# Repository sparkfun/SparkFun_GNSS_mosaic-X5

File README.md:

SparkFun Tri-band GNSS RTK Breakout - mosaic-X5
========================================

[*SparkFun Tri-band GNSS RTK Breakout - mosaic-X5 (GPS-23088)*](https://www.sparkfun.com/sparkfun-triband-gnss-rtk-breakout-mosaic-x5.html)

At the heart of the Triband GNSS RTK Breakout is [Septentrio](https://www.septentrio.com/en)'s mosaic-X5, a compact, low power, multi-band, multi-constellation, high-precision GNSS receiver. The receiver supports the GPS (USA), GLONASS (Russia), Beidou (China), Galileo (Europe), and NavIC (India) constellations, including regional systems *(i.e. SBAS and QZSS)*. With its [**Real Time Kinematics**](https://learn.sparkfun.com/tutorials/813) (RTK) capabilities, the module can achieve a horizontal accuracy of 6mm (~0.25in), vertical accuracy of 1cm (~0.4in) using RTK, and timing precision of 5ns (5 billionths of a second). It also features Septentrio's unique [AIM+ technology](https://www.septentrio.com/en/learn-more/advanced-positioning-technology/aim-jamming-protection) for interference mitigation and anti-spoofing, ensuring best-in-class reliability and scalable position accuracy.

The mosaic-X5 is a sophisticated chip running an internal web server that can be accessed through the USB interface with a standard browser using a Linux/Windows computer. Septentrio also provides dozens of [video tutorials](https://www.youtube.com/@SeptentrioGNSS/videos) to guide users through the configuration settings of their GNSS receivers utilizing the web interface.

Beyond the capabilities of the mosaic-X5 module, this board is seamless to operate with no programming skills required. Gone are the times when a microcontroller was required to interface with the GNSS receiver and log data to an SD card and when users had to carry around an SD card reader to extract the data from the SD card. The mosaic-X5 Triband GNSS RTK Breakout can start/stop logging data or mount/unmount the SD card, without a single line of code, just utilizing a simple button. For the users who prefer a command-line interface, Septentrio has you covered. Users can still control and configure the mosaic-X5 module through a CLI, which is useful for scenarios such as production line testing *(in fact, that is how we tested this board)*.

This breakout board is a perfect middle ground for users who would like to integrate the mosaic-X5 module into a project/enclosure with access to a majority of the module's available pins, similar to Septentrio's developer kit, but in the smaller form factor of their evaluation kit. Or maybe... you just needed a PPS output at a 3.3V logic level. *Please, check out our [hookup guide](https://docs.sparkfun.com/SparkFun_GNSS_mosaic-X5) for more details on the capabilities of this board (that we couldn't fit in this product description).*

Documentation
--------------

- **[Hookup Guide (mkdocs)](http://docs.sparkfun.com/SparkFun_GNSS_mosaic-X5/)** - Hookup guide for the mosaic-X5 GNSS Breakout hosted by GitHub pages.<br>

Repository Contents
-------------------

- **[/docs](/docs/)** - Online documentation files
  - [assets](/docs/assets/) - Assets files
    - [board_files](/docs/assets/board_files/) - Files for the product design
      - [Eagle design files](/docs/assets/board_files/eagle_files.zip) (.zip)
      - [Schematic](/docs/assets/board_files/schematic.pdf) (.pdf)
      - [Dimensions](/docs/assets/board_files/dimensions.pdf) (.pdf)
    - [component_documentation](/docs/assets/component_documentation/) - Datasheets for hardware components
    - [img/hookup_guide/](/docs/assets/img/hookup_guide/) - Images for hookup guide documentation
- **[/Hardware](/Hardware/)** - Eagle design files (.brd, .sch)
  - **[/Production](/Production/)** - Production files

Product Variants
----------------

- mosaic-X5:
  - [GPS-23088](https://www.sparkfun.com/sparkfun-triband-gnss-rtk-breakout-mosaic-x5.html) - Triband GNSS RTK Breakout - mosaic-X5
  - [SXM-E](https://www.sparkpnt.com/products/sparkpnt-sxm-e-cors) - RTK mosaic-X5
  - [GPS-24903](https://www.sparkfun.com/sparkpnt-rtk-facet-mosaic-l-band.html) - SparkPNT RTK Facet mosaic L-Band
  - Flex Modules:
    - [GPS-28138](https://www.sparkfun.com/sparkpnt-gnss-flex-module-mosaic-x5.html) - GNSS Flex module - mosaic-X5
    - [GPS-29457](https://www.sparkfun.com/sparkpnt-gnss-flex-module-mosaic-x5-im19-imu.html) - GNSS Flex module - mosaic-X5 & IM19
    - [GPS-28766](https://www.sparkfun.com/sparkfun-gnss-flex-phat-mosaic-x5.html) - GNSS Flex pHAT w/ the mosaic-X5 GNSS Flex module
    - [GPS-29889](https://www.sparkfun.com/sparkfun-gnss-flex-phat-mosaic-x5-im19-imu.html) - GNSS Flex pHAT w/ the mosaic-X5 & IM19 GNSS Flex module
- mosaic-G5 P3:
  - [GPS-29208]( - GNSS RTK Breakout - mosaic-G5 P3
  - Flex Modules:
    - [GPS-29209](https://www.sparkfun.com/sparkpnt-gnss-flex-module-mosaic-g5-p3.html) - GNSS Flex module - mosaic-G5 P3
    - [GPS-29363](https://www.sparkfun.com/sparkpnt-gnss-flex-module-mosaic-g5-p3-im19-imu.html) - GNSS Flex module - mosaic-G5 P3 & IM19
    - [GPS-](https://www.sparkfun.com/sparkfun-gnss-flex-phat-mosaic-g5-p3.html) - GNSS Flex pHAT w/ the mosaic-G5 P3 GNSS Flex module
    - [GPS-](https://www.sparkfun.com/sparkfun-gnss-flex-phat-mosaic-g5-p3-im19-imu.html) - GNSS Flex pHAT w/ the mosaic-G5 P3 & IM19 GNSS Flex module
- mosaic-T:
  - [GPS-28731](https://www.sparkfun.com/sparkfun-timing-gnss-breakout-mosaic-t.html) - mosaic-T Timing GNSS Breakout
  - [SXT](https://www.sparkpnt.com/products/sxt-gnssdo) - GNSS Disciplined Oscillator

Version History
---------------

- [v10](https://github.com/sparkfun/SparkFun_GNSS_mosaic-X5/releases/tag/v10) - Initial Release

License Information
-------------------

This product is ***open source***!

Please review the [`LICENSE.md`](./LICENSE.md) file for license information.

If you have any questions or concerns about licensing, please contact technical support on our [SparkFun forums](https://community.sparkfun.com/).

Distributed as-is; no warranty is given.

- Your friends at SparkFun.

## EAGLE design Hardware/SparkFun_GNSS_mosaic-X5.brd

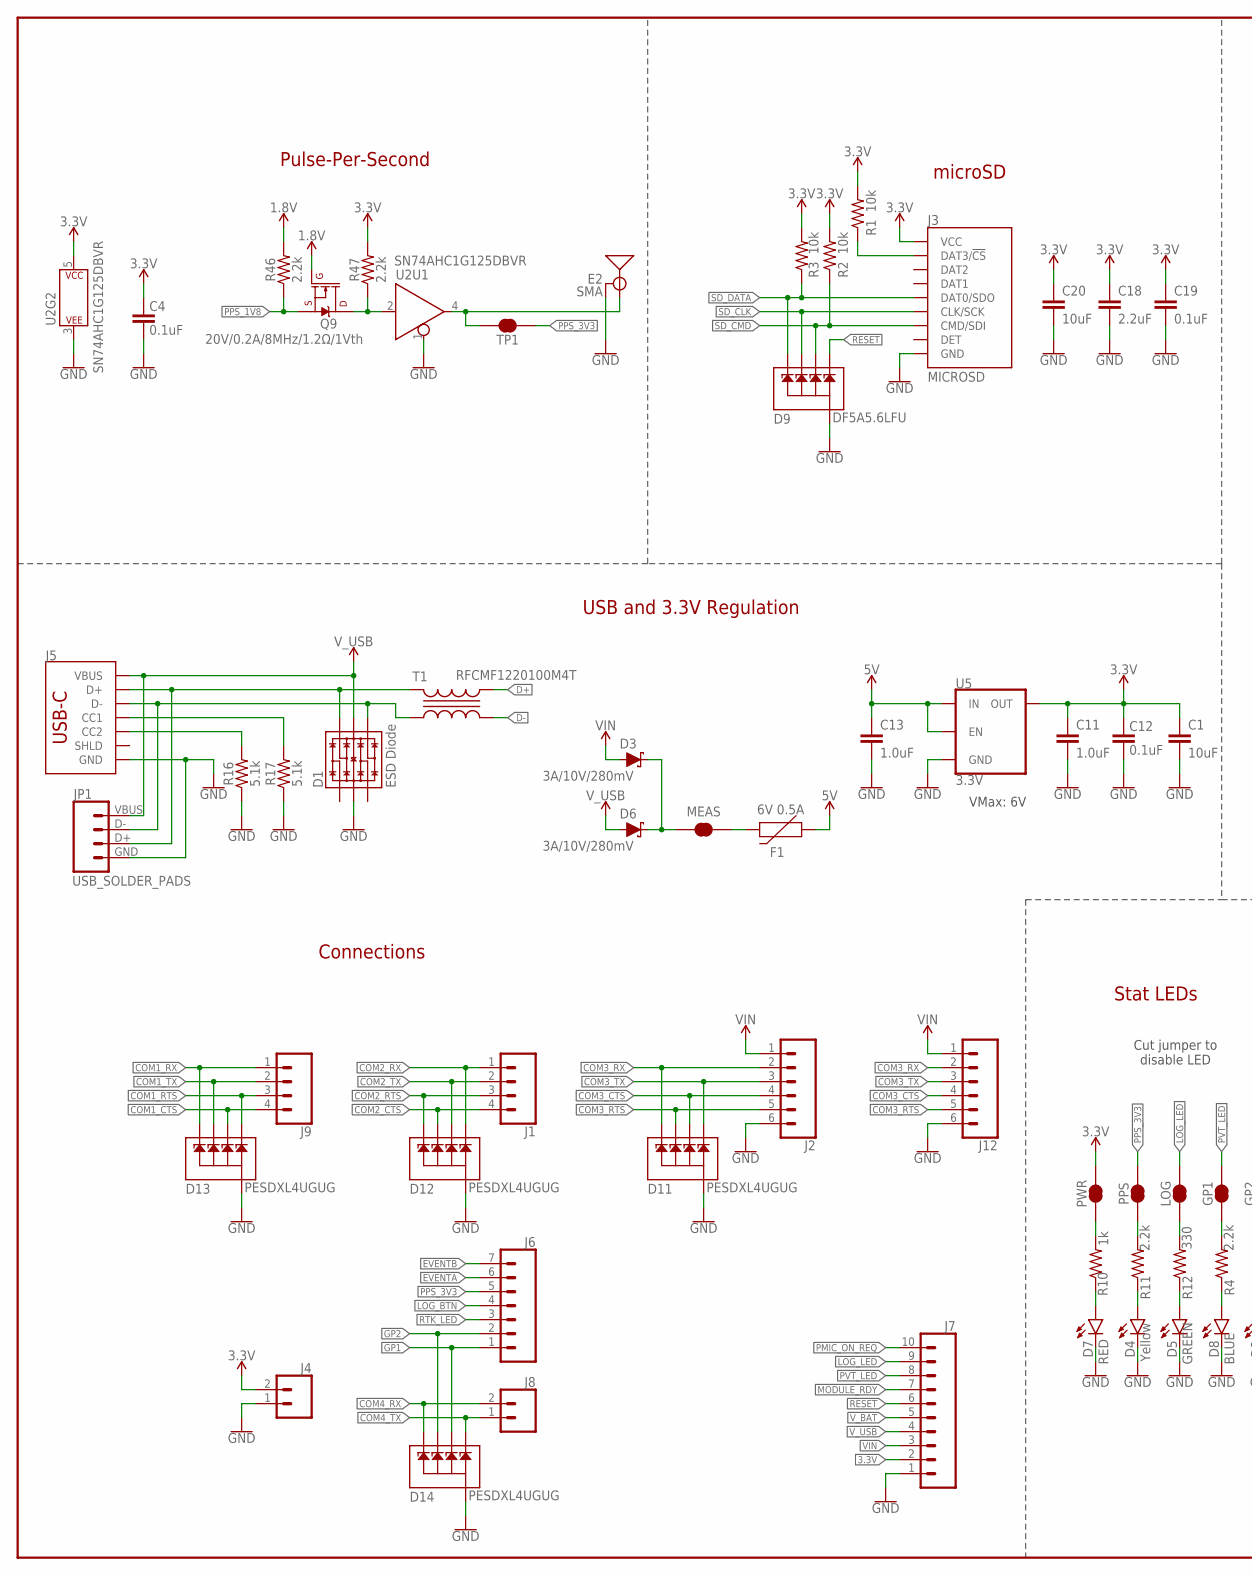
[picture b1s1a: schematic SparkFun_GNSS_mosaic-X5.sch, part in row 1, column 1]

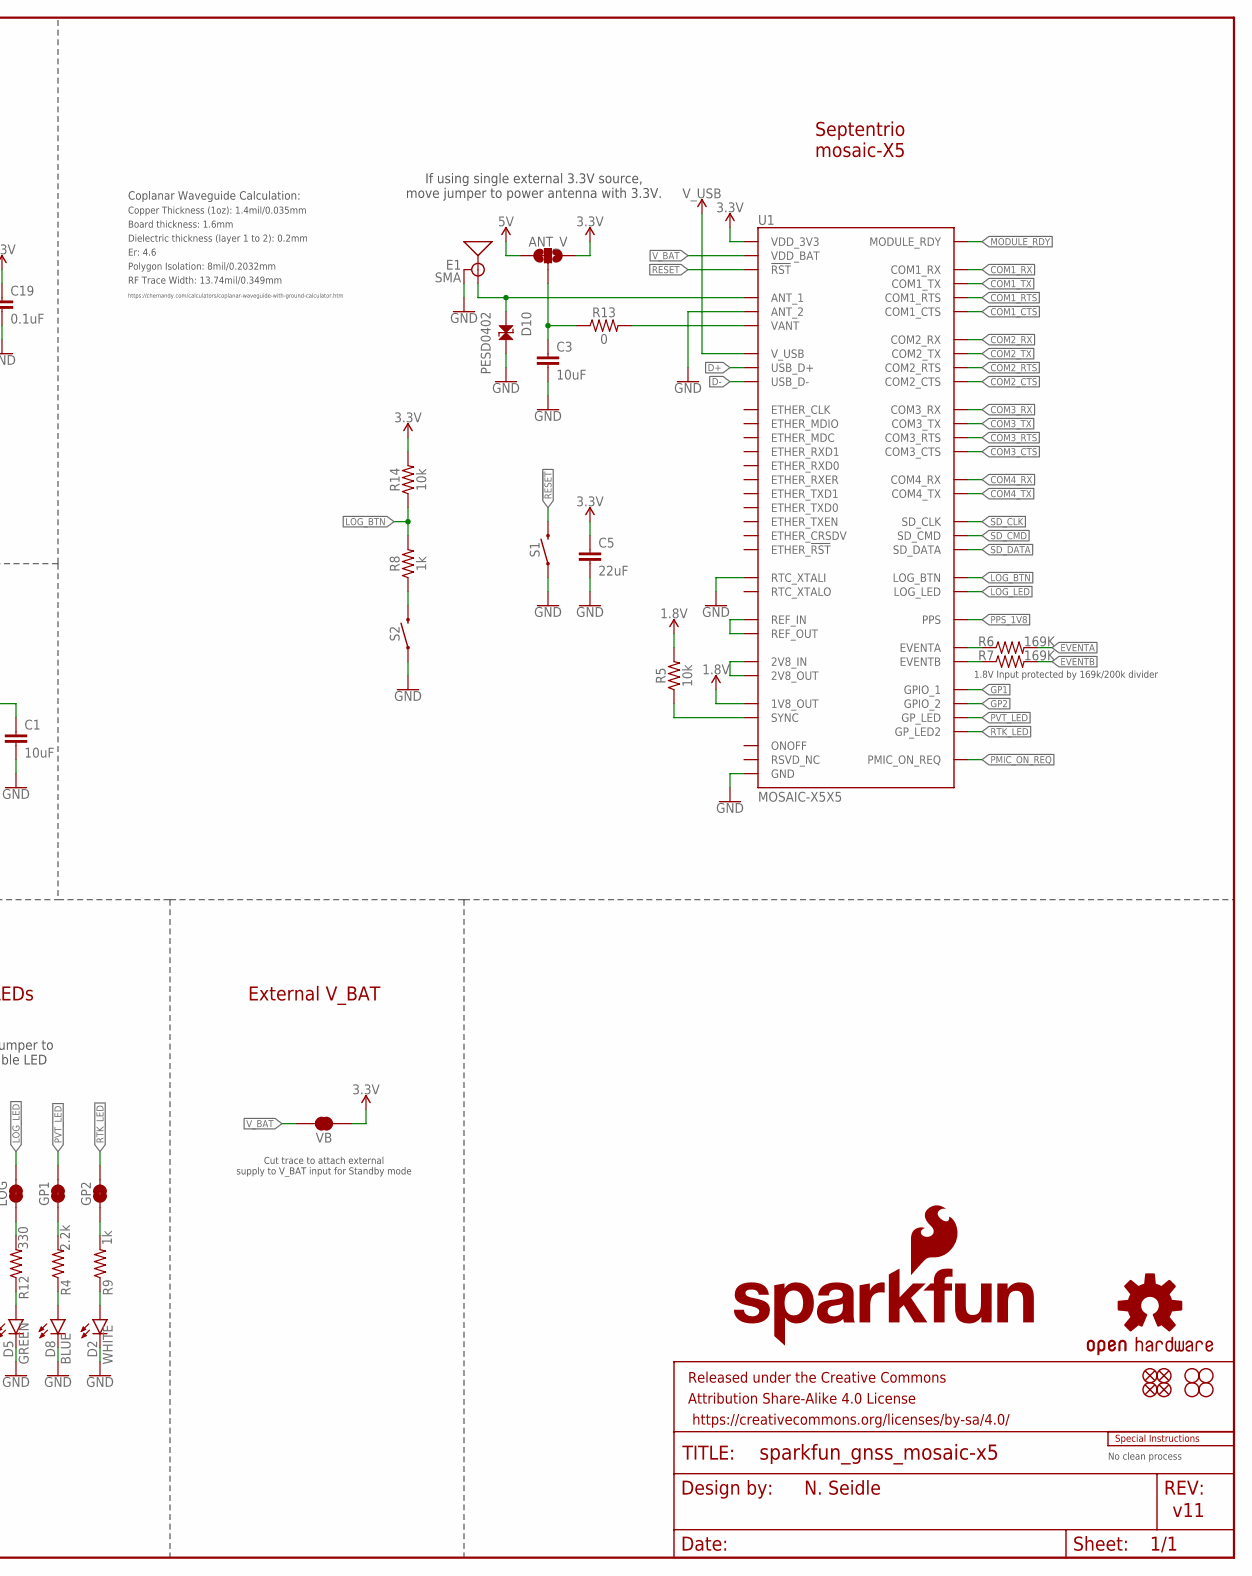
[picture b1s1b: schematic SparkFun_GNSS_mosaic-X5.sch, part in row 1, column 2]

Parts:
ANT_V: JUMPER-SMT_3_1-NC_TRACE_SILK; SMT-JUMPER_3_1-NC_TRACE_SILK
C1, C3, C20: 10uF; 0603
C4, C12, C19: 0.1uF; 0603
C5: 22uF; 0603
C11, C13: 1.0uF; 0603
C18: 2.2uF; 0603
D1: ESD Diode; SOT-23-6
D2: WHITE; LED-0603
D3, D6: 3A/10V/280mV; SOD-323
D4: Yellow; LED-0603
D5: GREEN; LED-0603
D7: RED; LED-0603
D8: BLUE; LED-0603
D9: DF5A5.6LFU; SOT353
D10: PESD0402; 0402-TIGHT
D11, D12, D13, D14: PESDXL4UGUG; SOT353
E1, E2: SMA; SMA-EDGE
F1: 6V 0.5A; 0805
FRAME2: FRAME-LEDGER; CREATIVE_COMMONS
GP1, GP2: JUMPER-SMT_2_NC_TRACE_SILK; SMT-JUMPER_2_NC_TRACE_SILK
H1, H2, H3, H4: STAND-OFF
J1, J9: CONN_041X04_NO_SILK_NO_POP; 1X04_NO_SILK
J2: CONN_06JST-SMD-LOCKING; JST-6-SMD-1.25MM-LOCKING
J3: MICROSD; MICROSD-EXTERNALPIN
J4, J8: CONN_021X02_NO_SILK; 1X02_NO_SILK
J5: USB Female Type C Connector; USB-C-16P_4LAYER-PADS
J6: CONN_07NO_SILK; 1X07_NO_SILK
J7: CONN_10NO_SILK_PTH_FEMALE; 1X10_NO_SILK
J12: CONN_06PAD; 1X06_SOLDER_PADS
JP1: USB_SOLDER_PADS; USB-SOLDER-PADS
JP21, JP61, JP71, JP81: FIDUCIALUFIDUCIAL; FIDUCIAL-MICRO
LOG: JUMPER-SMT_2_NC_TRACE_SILK; SMT-JUMPER_2_NC_TRACE_SILK
LOGO2: OSHW-LOGOMINI; OSHW-LOGO-MINI
LOGO4: SFE_LOGO_NAME_FLAME10_MM; SFE_LOGO_NAME_FLAME_10MM
MEAS: JUMPER-COMBO_2_NC_TRACE; COMBO-JUMPER_2_NC_TRACE
PPS: JUMPER-SMT_2_NC_TRACE_SILK; SMT-JUMPER_2_NC_TRACE_SILK
PWR: JUMPER-SMT_2_NC_TRACE_SILK; SMT-JUMPER_2_NC_TRACE_SILK
Q9: 20V/0.2A/8MHz/1.2Ω/1Vth; SOT-416FL
R1, R2, R3, R5, R14: 10k; 0603
R4, R11, R46, R47: 2.2k; 0603
R6, R7: 169K; 0603
R8, R9, R10: 1k; 0603
R12: 330; 0603
R13: 0; 0603
R16, R17: 5.1k; 0603
S1: MOMENTARY-SWITCH-SPST-SMD-4.6X2.8MM; TACTILE_SWITCH_SMD_4.6X2.8MM
S2: MOMENTARY-SWITCH-SPST-SMD-5.2-TALL-REDUNDANT; TACTILE_SWITCH_SMD_5.2MM
T1: RFCMF1220100M4T
TP1: JUMPER-SMT_2_NC_TRACE_SILK; SMT-JUMPER_2_NC_TRACE_SILK
U1: MOSAIC-X5X5; MOSAIC_LGA
U2: SN74AHC1G125DBVR; SOT23-5
U5: 3.3V; SOT23-5
U$2: SPECIAL_INSTRUCTIONS-ORDERING; ORDERING_INSTRUCTIONS
VB: JUMPER-SMT_2_NC_TRACE_SILK; SMT-JUMPER_2_NC_TRACE_SILK

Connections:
1.8V: Q9.1 (G), R5.2, R46.2, U1.AC4 (1V8_OUT)
3.3V: ANT_V.1, C1.1, C4.2, C5.1, C11.1, C12.2, C18.1, C19.1, C20.1, J3.4 (VCC), J4.2, J7.2, PWR.2, R1.2, R2.2, R3.2, R14.2, R47.2, U1.A18 (VDD_3V3), U1.A19 (VDD_3V3), U1.A20 (VDD_3V3), U1.B18 (VDD_3V3), U1.B19 (VDD_3V3), U1.B20 (VDD_3V3), U1.C18 (VDD_3V3), U1.C19 (VDD_3V3), U1.C20 (VDD_3V3), U2.5 (P$V+), U5.5 (OUT), VB.1
5V: ANT_V.3, C13.1, F1.1, U5.1 (IN), U5.3 (EN)
!RESET!: D9.3, J7.6, S1.3 (2), S1.4 (2), U1.A11 (!RST!)
ANT_V: ANT_V.2, C3.1, R13.1
CC1: J5.A5 (CC1), R17.2
CC2: J5.B5 (CC2), R16.2
COM1_CTS: D13.4, J9.4, U1.E1 (COM1_CTS)
COM1_RTS: D13.3, J9.3, U1.C1 (COM1_RTS)
COM1_RX: D13.1, J9.1, U1.B1 (COM1_RX)
COM1_TX: D13.5, J9.2, U1.D1 (COM1_TX)
COM2_CTS: D12.5, J1.4, U1.J1 (COM2_CTS)
COM2_RTS: D12.1, J1.3, U1.G1 (COM2_RTS)
COM2_RX: D12.3, J1.1, U1.F1 (COM2_RX)
COM2_TX: D12.4, J1.2, U1.H1 (COM2_TX)
COM3_CTS: D11.4, J2.4, J12.4, U1.N1 (COM3_CTS)
COM3_RTS: D11.5, J2.5, J12.5, U1.L1 (COM3_RTS)
COM3_RX: D11.1, J2.2, J12.2, U1.K1 (COM3_RX)
COM3_TX: D11.3, J2.3, J12.3, U1.M1 (COM3_TX)
COM4_RX: D14.1, J8.2, U1.D3 (COM4_RX)
COM4_TX: D14.3, J8.1, U1.E3 (COM4_TX)
D+: T1.B2, U1.A5 (USB_D+)
D-: T1.A2, U1.A6 (USB_D-)
EVENTA: J6.6, R6.2
EVENTB: J6.7, R7.2
GND: C1.2, C3.2, C4.1, C5.2, C11.2, C12.1, C13.2, C18.2, C19.2, C20.2, D1.2 (VSS), D2.C, D4.C, D5.C, D7.C, D8.C, D9.2, D10.2, D11.2, D12.2, D13.2, D14.2, E1.GND@0 (GND), E1.GND@1 (GND), E1.GND@2 (GND), E1.GND@3 (GND), E2.GND@0 (GND), E2.GND@1 (GND), E2.GND@2 (GND), E2.GND@3 (GND), J2.6, J3.6 (GND), J3.10 (GND), J3.11 (GND), J3.12 (GND), J3.13 (GND), J4.1, J5.GND, J5.GND2 (GND), J7.1, J12.6, JP1.GND (4), R16.1, R17.1, S1.1, S1.2 (1), S2.1, S2.2 (1), U1.A3 (RTC_XTALI), U1.A4 (GND), U1.A7 (GND), U1.A15 (GND), U1.A16 (GND), U1.A17 (GND), U1.A21 (GND), U1.A22 (GND), U1.A23 (GND), U1.AA13 (GND), U1.AA14 (GND), U1.AA15 (GND), U1.AA16 (GND), U1.AA17 (GND), U1.AA18 (GND), U1.AA19 (GND), U1.AA20 (GND), U1.AA21 (GND), U1.AA22 (GND), U1.AA23 (GND), U1.AB2 (GND), U1.AB3 (GND), U1.AB4 (GND), U1.AB5 (GND), U1.AB6 (GND), U1.AB7 (GND), U1.AB8 (GND), U1.AB13 (GND), U1.AB14 (GND), U1.AB15 (GND), U1.AB16 (GND), U1.AB17 (GND), U1.AB18 (GND), U1.AB19 (GND), U1.AB20 (GND), U1.AB21 (GND), U1.AB22 (GND), U1.AB23 (GND), U1.AC13 (GND), U1.AC15 (GND), U1.AC18 (GND), U1.AC19 (GND), U1.AC21 (GND), U1.AC22 (GND), U1.AC23 (GND), U1.B4 (GND), U1.B5 (GND), U1.B6 (GND), U1.B7 (GND), U1.B13 (GND), U1.B17 (GND), U1.B21 (GND), U1.C4 (GND), U1.C7 (GND), U1.C15 (GND), U1.C16 (GND), U1.C17 (GND), U1.C23 (GND), U1.D2 (GND), U1.D21 (GND), U1.D22 (GND), U1.D23 (GND), U1.E2 (GND), U1.E21 (GND), U1.E22 (GND), U1.E23 (GND), U1.F21 (GND), U1.F22 (GND), U1.F23 (GND), U1.G2 (GND), U1.G21 (GND), U1.G23 (GND), U1.H21 (GND), U1.H22 (GND), U1.H23 (GND), U1.J21 (GND), U1.J22 (GND), U1.J23 (GND), U1.K2 (GND), U1.K21 (GND), U1.K22 (GND), U1.K23 (GND), U1.L21 (GND), U1.L22 (GND), U1.L23 (GND), U1.M21 (GND), U1.M22 (GND), U1.N21 (GND), U1.N22 (GND), U1.P1 (GND), U1.P2 (GND), U1.P3 (GND), U1.P21 (GND), U1.P22 (GND), U1.R3 (GND), U1.R21 (GND), U1.R22 (GND), U1.T21 (GND), U1.T22 (GND), U1.T23 (GND), U1.U2 (GND), U1.U21 (GND), U1.U22 (GND), U1.U23 (GND), U1.V21 (GND), U1.V22 (GND), U1.V23 (ANT_2), U1.W21 (GND), U1.W22 (GND), U1.W23 (GND), U1.Y2 (GND)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
GP1: D14.4, J6.1, U1.AA4 (GPIO_1)
GP2: D14.5, J6.2, U1.L3 (GPIO_2)
GPS_ANT1: D10.1, E1.SIG (SIGNAL), U1.AC20 (ANT_1)
LOG_BTN: J6.4, R8.2, R14.1, U1.K3 (LOG_BTN)
LOG_LED: J7.9, LOG.2, U1.B2 (LOG_LED)
MEAS: D3.C, D6.C, MEAS.2, MEAS.4 (2)
MODULE_RDY: J7.7, U1.A12 (MODULE_RDY)
unnamed: R8.1, S2.3 (2), S2.4 (2)
unnamed: D4.A, R11.1
unnamed: PPS.1, R11.2
unnamed: F1.2, MEAS.1, MEAS.3 (1)
unnamed: J3.2 (DAT3/!CS!), R1.1
unnamed: R6.1, U1.AC6 (EVENTA)
unnamed: R7.1, U1.AC7 (EVENTB)
unnamed: D2.A, R9.1
unnamed: GP2.1, R9.2
unnamed: U1.AC16 (REF_OUT), U1.AC17 (REF_IN)
unnamed: D8.A, R4.1
unnamed: GP1.1, R4.2
unnamed: D7.A, R10.1
unnamed: U1.M23 (2V8_IN), U1.N23 (2V8_OUT)
unnamed: D5.A, R12.1
unnamed: LOG.1, R12.2
unnamed: PWR.1, R10.2
unnamed: R5.1, U1.AC3 (SYNC)
PMIC_ON_REQ: J7.10, U1.B16 (PMIC_ON_REQ)
PPS: E2.SIG (SIGNAL), TP1.2, U2.4 (Y)
PPS_1V8: Q9.2 (S), R46.1, U1.AC8 (PPS)
PPS_3: Q9.3 (D), R47.1, U2.2 (A)
PPS_3V3: J6.5, PPS.2, TP1.1
PVT_LED: GP1.2, J7.8, U1.A14 (GP_LED)
RTK_LED: GP2.2, J6.3, U1.M3 (GP_LED2)
SD_CLK: D9.5, J3.5 (CLK/SCK), U1.AA1 (SD_CLK)
SD_CMD: D9.4, J3.3 (CMD/SDI), R2.1, U1.AB1 (SD_CMD)
SD_DATA: D9.1, J3.7 (DAT0/SDO), R3.1, U1.Y1 (SD_DATA)
USB_D+: D1.6 (IO4), J5.A6 (D+), J5.B6 (D+), JP1.D+ (3), T1.B1
USB_D-: D1.4 (IO3), J5.A7 (D-), J5.B7 (D-), JP1.D- (2), T1.A1
VANT: R13.2, U1.P23 (VANT), U1.R23 (VANT)
VIN: D3.A, J2.1, J7.3, J12.1
V_BAT: J7.5, U1.B8 (VDD_BAT), VB.2
V_USB: D1.5 (VCC), D6.A, J5.VBUS1 (VBUS), J5.VBUS2 (VBUS), J7.4, JP1.VBUS (1), U1.A8 (V_USB)

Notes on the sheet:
v11
Board thickness: 1.6mm
Er: 4.6
Copper Thickness (1oz): 1.4mil/0.035mm
RF Trace Width: 13.74mil/0.349mm
Polygon Isolation: 8mil/0.2032mm
No clean process
Dielectric thickness (layer 1 to 2): 0.2mm
https://chemandy.com/calculators/coplanar-waveguide-with-ground-calculator.htm
Coplanar Waveguide Calculation:
USB and 3.3V Regulation
N. Seidle
Cut jumper to disable LED
Stat LEDs
Connections
microSD
Pulse-Per-Second
External V_BAT
Cut trace to attach external supply to V_BAT input for Standby mode
Septentrio mosaic-X5
1.8V Input protected by 169k/200k divider
VMax: 6V
If using single external 3.3V source, move jumper to power antenna with 3.3V.

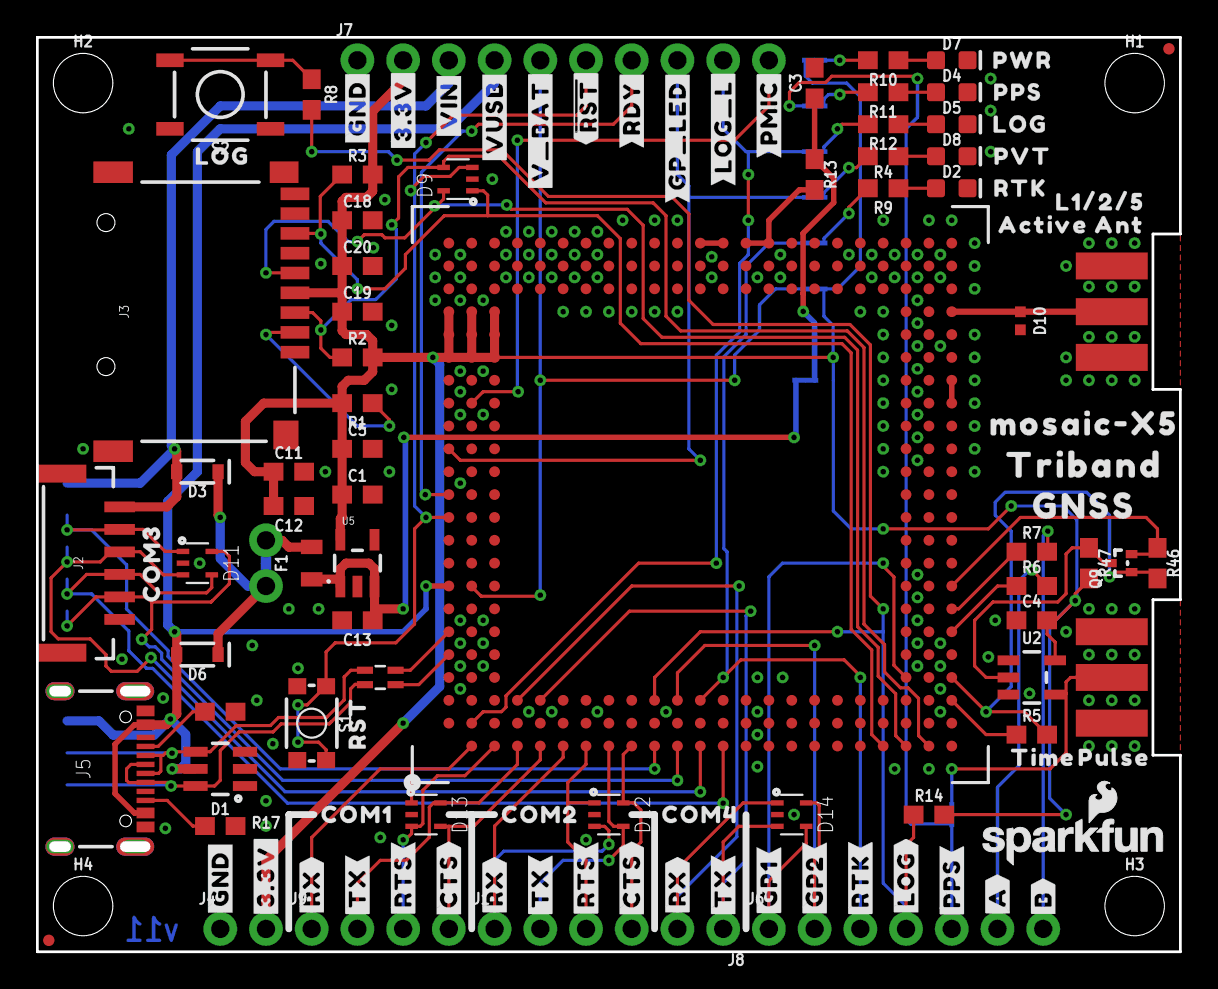
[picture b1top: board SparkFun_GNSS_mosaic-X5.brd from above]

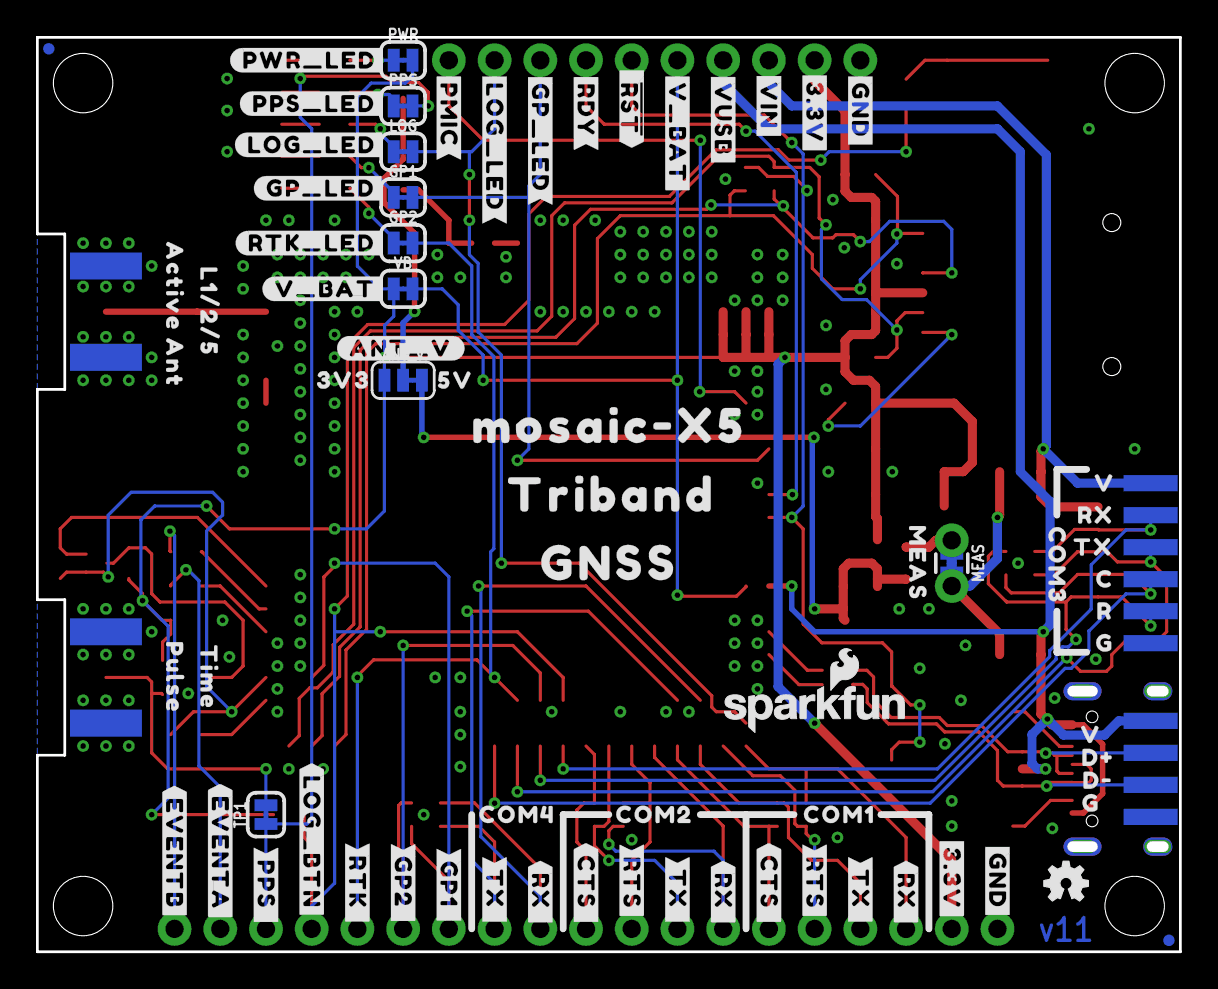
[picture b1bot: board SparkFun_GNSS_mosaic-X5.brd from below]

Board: 4 copper layers, 63.5 x 50.8 mm, 192 parts (75 on the bottom side), 67 nets.

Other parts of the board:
LOGO1: SFE_LOGO_NAME_FLAME10_MM; SFE_LOGO_NAME_FLAME_10MM
U$1: V0
U$3: GNSS_1
U$4: TRIBAND_2
U$5: MEAS0
U$6, U$135: _ACTIVE_ANT1
U$7: #RTK#0
U$8: C4
U$9: D#2
U$10: D#3
U$11: G0
U$12: R5
U$13: RST0
U$14: RX7
U$15: TX6
U$16: V8
U$17: #EVENTA#0
U$18, U$82: COM30
U$19: MOSAIC#X50
U$20: MOSAIC#X5_0
U$21, U$136: TIME0
U$22: G1
U$23: 3V30
U$24: 5V0
U$25, U$137: PULSE1
U$26: #ANT_V#0
U$27: #RTK_LED#0
U$28: RTK0
U$29: PVT0
U$30: #GP1_#0
U$31: LOG0
U$33: #GP2_#0
U$34: #PPS_#0
U$35: #LOG_BTN#0
U$36: #LOG_L#0
U$37: #RDY#0
U$38: #GP_LED#0
U$39: #LOG_LED#0
U$40: #PMIC#0
U$41, U$42: #RTS#0
U$43: #RTK_#0
U$44: #EVENTB#0
U$69, U$134: L1#2#50
U$79: LOG2
U$80: PPS0
U$81: PWR3
U$83, U$99: COM20
U$84, U$109: COM10
U$85, U$108: COM40
U$87, U$93, U$110, U$114: #3#3V#1
U$88, U$100: #CTS#4
U$89, U$95, U$113, U$117: #GND#0
U$90, U$101: #RTS#5
U$91, U$102, U$111: #RX#2
U$92, U$103, U$112: #TX#3
U$94, U$104: #CTS_#4
U$97, U$106, U$115: #RX_#2
U$98, U$107, U$116: #TX_#3
U$118: ##RST##2
U$119: #GP_LED#4
U$121: #PMIC#6
U$122: #RDY#3
U$123, U$130: #VIN#1
U$124, U$131: #VUSB#0
U$125, U$132: #V_BAT#7
U$133: #_#RST##2
U$138: GNSS1
U$140: TRIBAND2
U$141: #LOG_LED#2
U$142: #PPS_LED#1
U$143: #GP_LED#3
U$144: #PWR_LED#0
U$145: #V_BAT#4
U$146: #A#8
U$147: #B#10
U$150: #GP1#0
U$152: #GP2#1
U$154: #LOG#4
U$156: #PPS#6

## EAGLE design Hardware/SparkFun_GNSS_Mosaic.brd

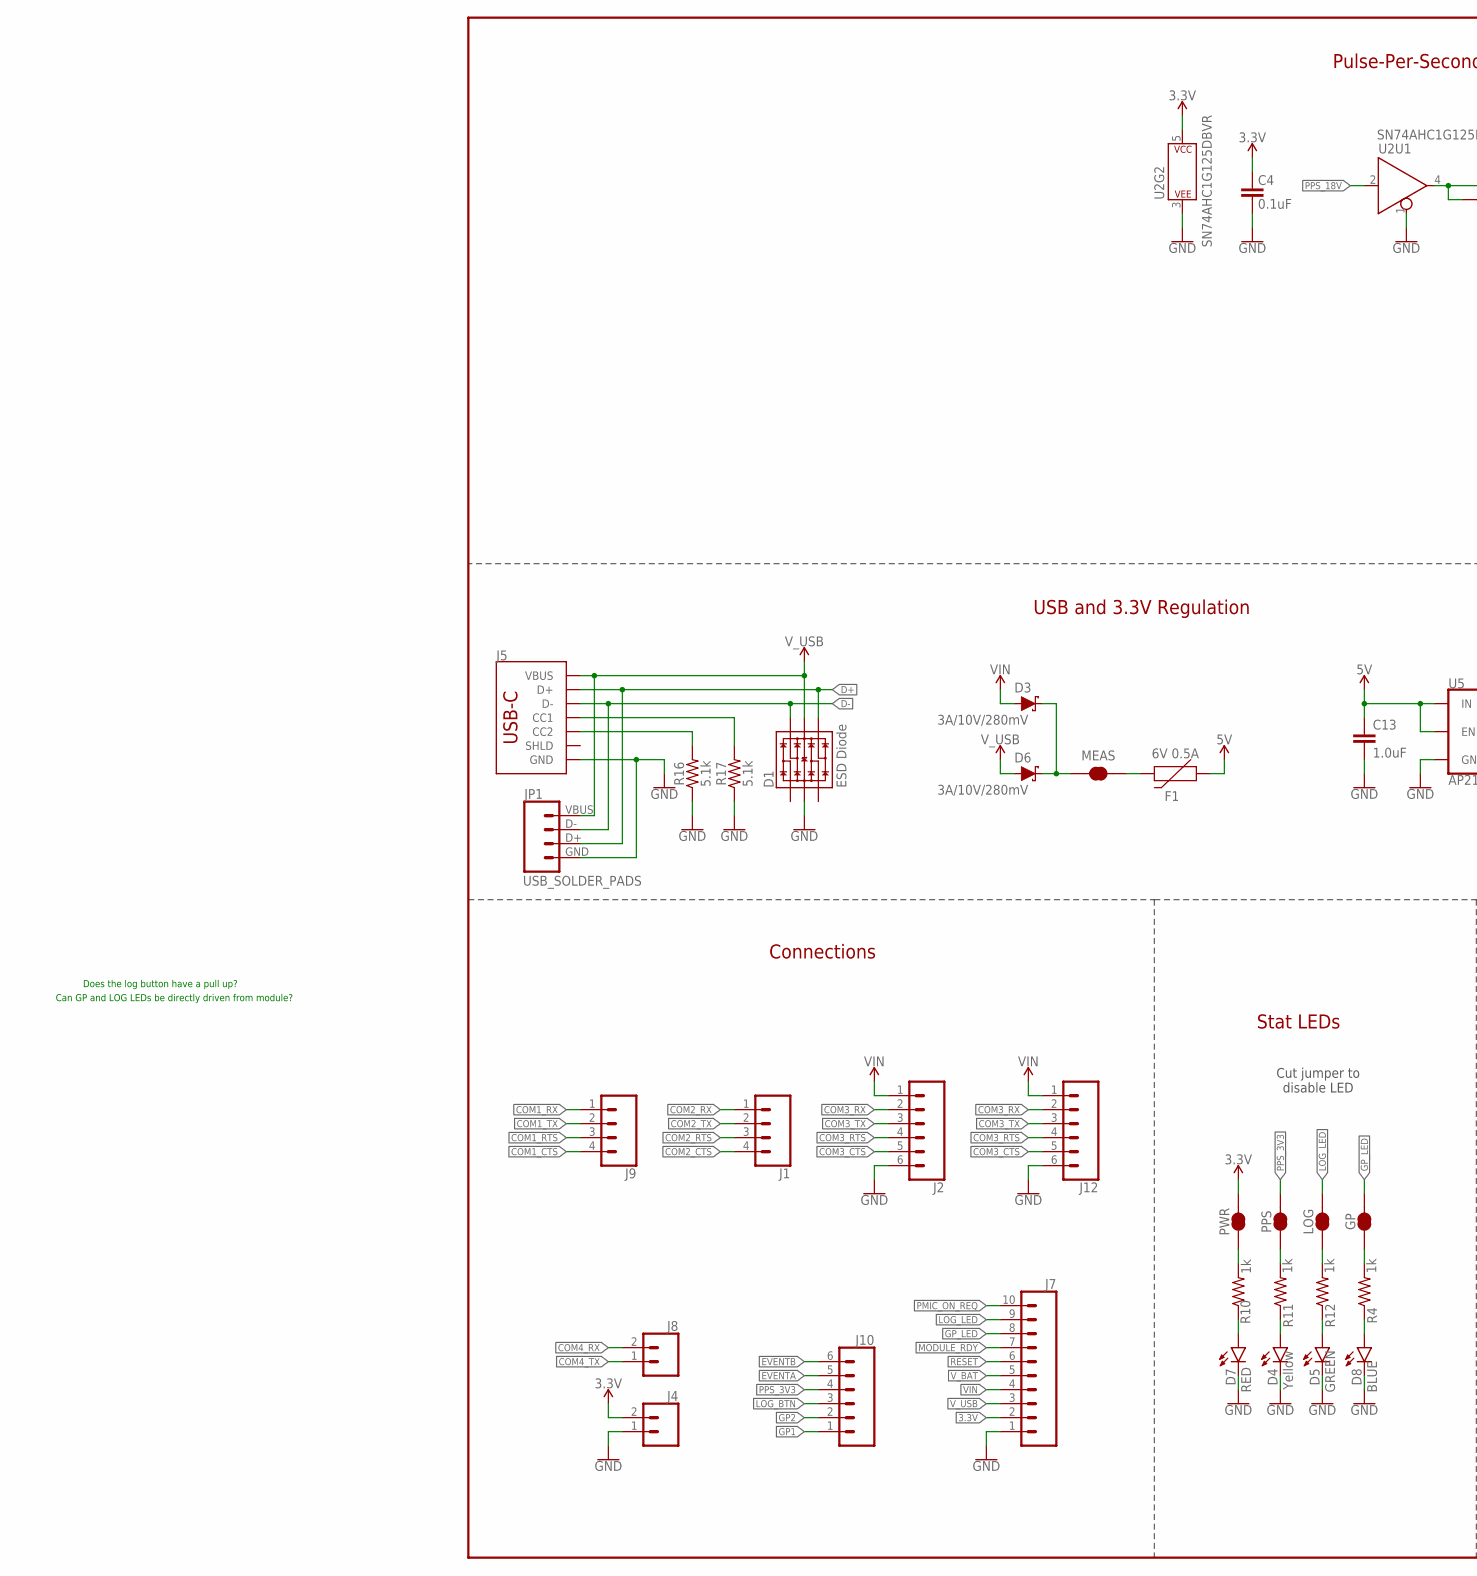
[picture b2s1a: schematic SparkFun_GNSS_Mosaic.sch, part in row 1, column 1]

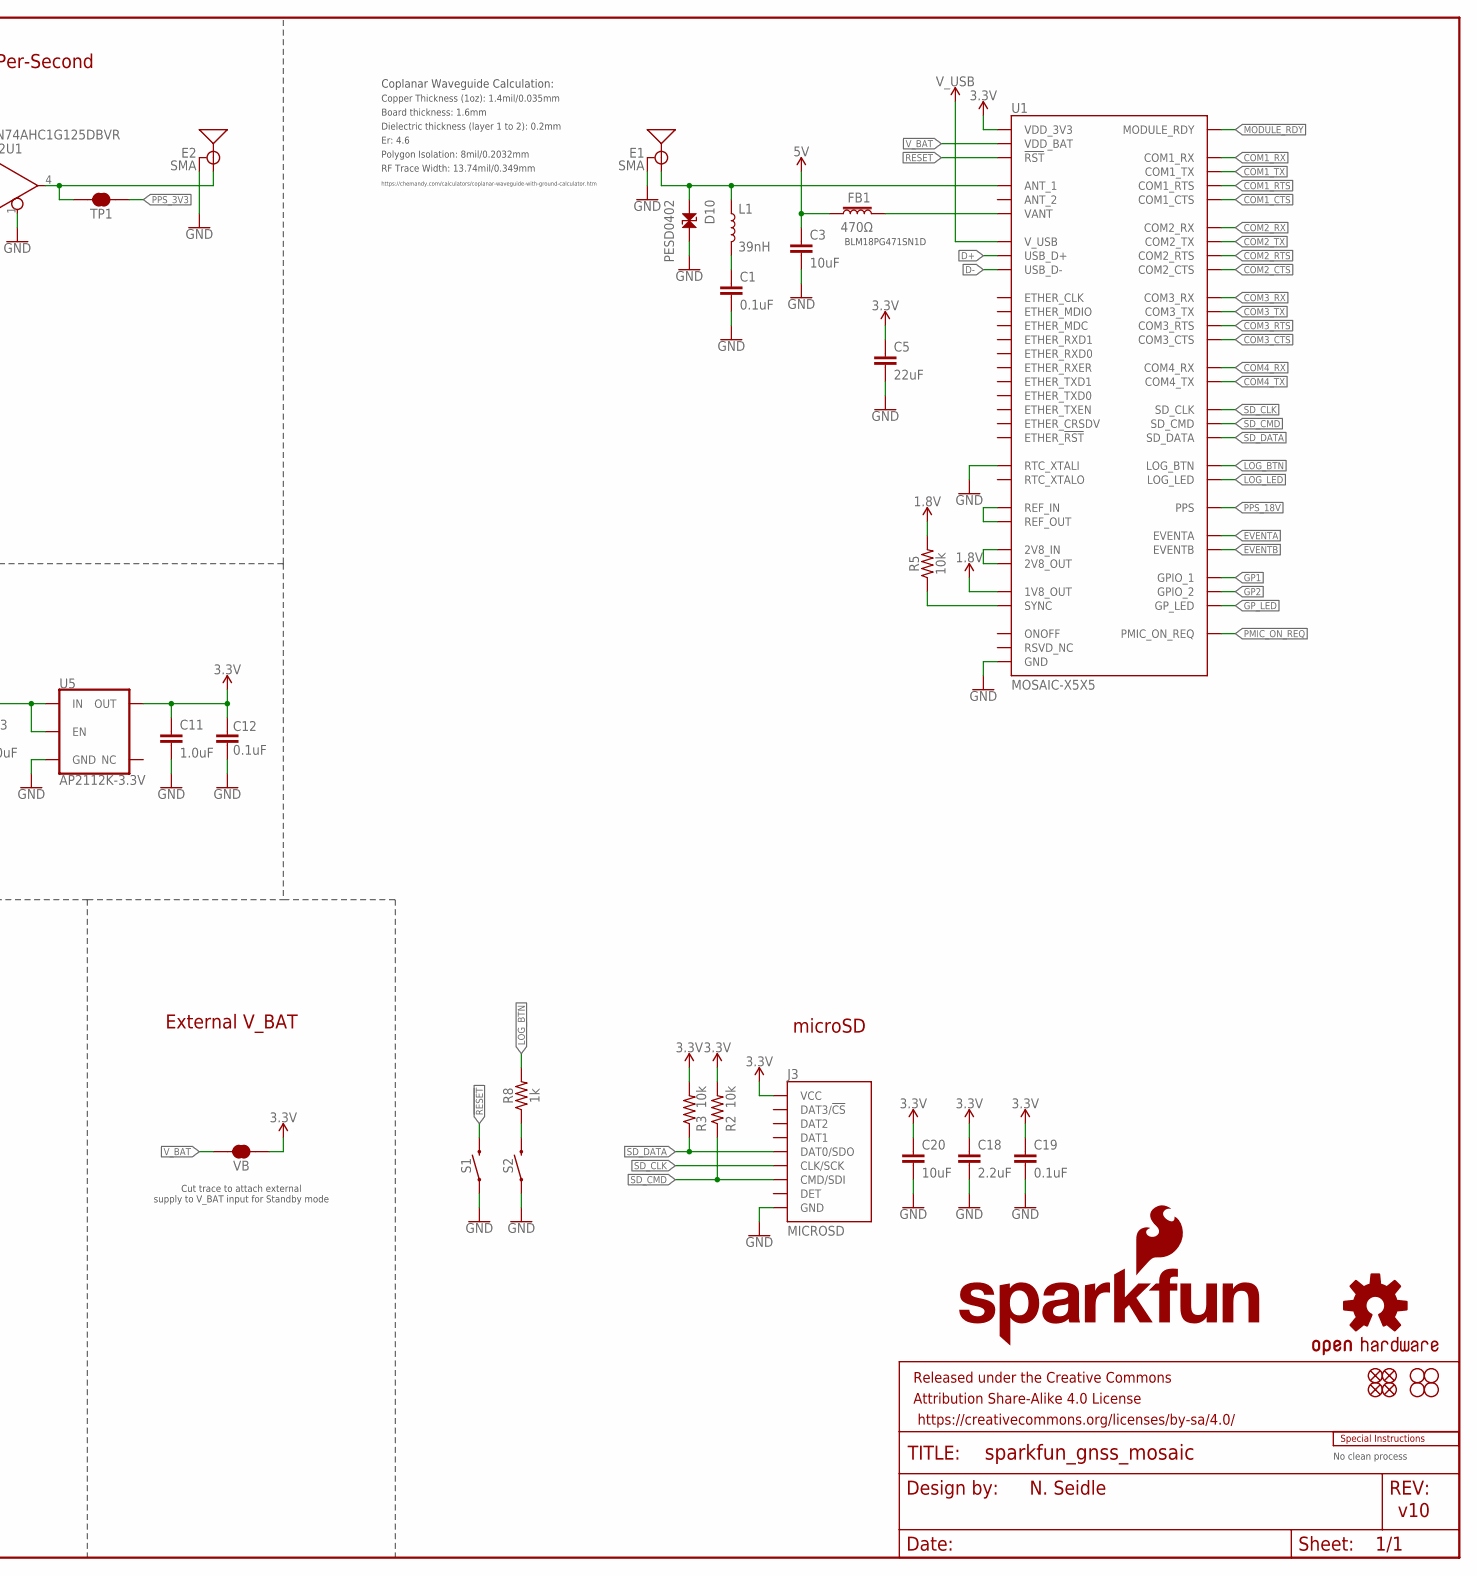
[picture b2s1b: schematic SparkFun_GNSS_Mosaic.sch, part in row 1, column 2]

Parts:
C1, C4, C12, C19: 0.1uF; 0603
C3, C20: 10uF; 0603
C5: 22uF; 0603
C11, C13: 1.0uF; 0603
C18: 2.2uF; 0603
D1: ESD Diode; SOT-23-6
D3, D6: 3A/10V/280mV; SOD-323
D4: Yellow; LED-0603
D5: GREEN; LED-0603
D7: RED; LED-0603
D8: BLUE; LED-0603
D10: PESD0402; 0402-TIGHT
E1, E2: SMA; SMA-EDGE
F1: 6V 0.5A; 0805
FB1: 470Ω; 0603
FRAME2: FRAME-LEDGER; CREATIVE_COMMONS
GP: JUMPER-SMT_2_NC_TRACE_SILK; SMT-JUMPER_2_NC_TRACE_SILK
H1, H2, H3, H4: STAND-OFF
J1, J9: CONN_041X04_NO_SILK_NO_POP; 1X04_NO_SILK
J2: CONN_06JST-SMD-LOCKING; JST-6-SMD-1.25MM-LOCKING
J3: MICROSD; MICROSD-EXTERNALPIN
J4, J8: CONN_021X02_NO_SILK; 1X02_NO_SILK
J5: USB Female Type C Connector; USB-C-16P_4LAYER-PADS
J7: CONN_10NO_SILK_PTH_FEMALE; 1X10_NO_SILK
J10: CONN_06NO_SILK_FEMALE_PTH; 1X06_NO_SILK
J12: CONN_06PAD; 1X06_SOLDER_PADS
JP1: USB_SOLDER_PADS; USB-SOLDER-PADS
JP21, JP61, JP71, JP81: FIDUCIALUFIDUCIAL; FIDUCIAL-MICRO
L1: 39nH; 0603
LOG: JUMPER-SMT_2_NC_TRACE_SILK; SMT-JUMPER_2_NC_TRACE_SILK
LOGO2: OSHW-LOGOMINI; OSHW-LOGO-MINI
LOGO4: SFE_LOGO_NAME_FLAME10_MM; SFE_LOGO_NAME_FLAME_10MM
MEAS: JUMPER-COMBO_2_NC_TRACE; COMBO-JUMPER_2_NC_TRACE
PPS: JUMPER-SMT_2_NC_TRACE_SILK; SMT-JUMPER_2_NC_TRACE_SILK
PWR: JUMPER-SMT_2_NC_TRACE_SILK; SMT-JUMPER_2_NC_TRACE_SILK
R2, R3, R5: 10k; 0603
R4, R8, R10, R11, R12: 1k; 0603
R16, R17: 5.1k; 0603
S1: MOMENTARY-SWITCH-SPST-SMD-4.6X2.8MM; TACTILE_SWITCH_SMD_4.6X2.8MM
S2: MOMENTARY-SWITCH-SPST-SMD-5.2-TALL-REDUNDANT; TACTILE_SWITCH_SMD_5.2MM
TP1: JUMPER-SMT_2_NC_TRACE_SILK; SMT-JUMPER_2_NC_TRACE_SILK
U1: MOSAIC-X5X5; MOSAIC-X5
U2: SN74AHC1G125DBVR; SOT23-5
U5: AP2112K-3.3V; SOT23-5
U$2: SPECIAL_INSTRUCTIONS-ORDERING; ORDERING_INSTRUCTIONS
VB: JUMPER-SMT_2_NC_TRACE_SILK; SMT-JUMPER_2_NC_TRACE_SILK

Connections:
1.8V: R5.2, U1.AC4 (1V8_OUT)
3.3V: C4.2, C5.1, C11.1, C12.2, C18.1, C19.1, C20.1, J3.4 (VCC), J4.2, J7.2, PWR.2, R2.2, R3.2, U1.A18 (VDD_3V3), U1.A19 (VDD_3V3), U1.A20 (VDD_3V3), U1.B18 (VDD_3V3), U1.B19 (VDD_3V3), U1.B20 (VDD_3V3), U1.C18 (VDD_3V3), U1.C19 (VDD_3V3), U1.C20 (VDD_3V3), U2.5 (P$V+), U5.5 (OUT), VB.1
5V: C3.1, C13.1, F1.1, FB1.1, U5.1 (IN), U5.3 (EN)
!RESET!: J7.6, S1.3 (2), S1.4 (2), U1.A11 (!RST!)
ANT_VCC: C1.1, L1.2
CC1: J5.A5 (CC1), R17.2
CC2: J5.B5 (CC2), R16.2
COM1_CTS: J9.4, U1.E1 (COM1_CTS)
COM1_RTS: J9.3, U1.C1 (COM1_RTS)
COM1_RX: J9.1, U1.B1 (COM1_RX)
COM1_TX: J9.2, U1.D1 (COM1_TX)
COM2_CTS: J1.4, U1.J1 (COM2_CTS)
COM2_RTS: J1.3, U1.G1 (COM2_RTS)
COM2_RX: J1.1, U1.F1 (COM2_RX)
COM2_TX: J1.2, U1.H1 (COM2_TX)
COM3_CTS: J2.5, J12.5, U1.N1 (COM3_CTS)
COM3_RTS: J2.4, J12.4, U1.L1 (COM3_RTS)
COM3_RX: J2.2, J12.2, U1.K1 (COM3_RX)
COM3_TX: J2.3, J12.3, U1.M1 (COM3_TX)
COM4_RX: J8.2, U1.D3 (COM4_RX)
COM4_TX: J8.1, U1.E3 (COM4_TX)
D+: D1.4 (IO3), J5.A6 (D+), J5.B6 (D+), JP1.D+ (3), U1.A5 (USB_D+)
D-: D1.6 (IO4), J5.A7 (D-), J5.B7 (D-), JP1.D- (2), U1.A6 (USB_D-)
EVENTA: J10.5, U1.AC6 (EVENTA)
EVENTB: J10.6, U1.AC7 (EVENTB)
GND: C1.2, C3.2, C4.1, C5.2, C11.2, C12.1, C13.2, C18.2, C19.2, C20.2, D1.2 (VSS), D4.C, D5.C, D7.C, D8.C, D10.2, E1.GND@0 (GND), E1.GND@1 (GND), E1.GND@2 (GND), E1.GND@3 (GND), E2.GND@0 (GND), E2.GND@1 (GND), E2.GND@2 (GND), E2.GND@3 (GND), J2.6, J3.6 (GND), J3.10 (GND), J3.11 (GND), J3.12 (GND), J3.13 (GND), J4.1, J5.GND, J5.GND2 (GND), J7.1, J12.6, JP1.GND (4), R16.1, R17.1, S1.1, S1.2 (1), S2.1, S2.2 (1), U1.A3 (RTC_XTALI), U1.A4 (GND), U1.A7 (GND), U1.A15 (GND), U1.A16 (GND), U1.A17 (GND), U1.A21 (GND), U1.A22 (GND), U1.A23 (GND), U1.AA13 (GND), U1.AA14 (GND), U1.AA15 (GND), U1.AA16 (GND), U1.AA17 (GND), U1.AA18 (GND), U1.AA19 (GND), U1.AA20 (GND), U1.AA21 (GND), U1.AA22 (GND), U1.AA23 (GND), U1.AB2 (GND), U1.AB3 (GND), U1.AB4 (GND), U1.AB5 (GND), U1.AB6 (GND), U1.AB7 (GND), U1.AB8 (GND), U1.AB13 (GND), U1.AB14 (GND), U1.AB15 (GND), U1.AB16 (GND), U1.AB17 (GND), U1.AB18 (GND), U1.AB19 (GND), U1.AB20 (GND), U1.AB21 (GND), U1.AB22 (GND), U1.AB23 (GND), U1.AC13 (GND), U1.AC15 (GND), U1.AC18 (GND), U1.AC19 (GND), U1.AC21 (GND), U1.AC22 (GND), U1.AC23 (GND), U1.B4 (GND), U1.B5 (GND), U1.B6 (GND), U1.B7 (GND), U1.B13 (GND), U1.B17 (GND), U1.B21 (GND), U1.C4 (GND), U1.C7 (GND), U1.C15 (GND), U1.C16 (GND), U1.C17 (GND), U1.C23 (GND), U1.D2 (GND), U1.D21 (GND), U1.D22 (GND), U1.D23 (GND), U1.E2 (GND), U1.E21 (GND), U1.E22 (GND), U1.E23 (GND), U1.F21 (GND), U1.F22 (GND), U1.F23 (GND), U1.G2 (GND), U1.G21 (GND), U1.G23 (GND), U1.H21 (GND), U1.H22 (GND), U1.H23 (GND), U1.J21 (GND), U1.J22 (GND), U1.J23 (GND), U1.K2 (GND), U1.K21 (GND), U1.K22 (GND), U1.K23 (GND), U1.L21 (GND), U1.L22 (GND), U1.L23 (GND), U1.M21 (GND), U1.M22 (GND), U1.N21 (GND), U1.N22 (GND), U1.P1 (GND), U1.P2 (GND), U1.P3 (GND), U1.P21 (GND), U1.P22 (GND), U1.R3 (GND), U1.R21 (GND), U1.R22 (GND), U1.T21 (GND), U1.T22 (GND), U1.T23 (GND), U1.U2 (GND), U1.U21 (GND), U1.U22 (GND), U1.U23 (GND), U1.V21 (GND), U1.V22 (GND), U1.W21 (GND), U1.W22 (GND), U1.W23 (GND), U1.Y2 (GND), U1.Y21 (GND), U1.Y22 (GND), U1.Y23 (GND), U2.1 (!EN), U2.3 (P$V-), U5.2 (GND)
GP1: J10.1, U1.AA4 (GPIO_1)
GP2: J10.2, U1.L3 (GPIO_2)
GPS_ANT1: D10.1, E1.SIG (SIGNAL), L1.1, U1.AC20 (ANT_1)
GP_LED: GP.2, J7.8, U1.A14 (GP_LED)
LOG_BTN: J10.3, R8.2, U1.K3 (LOG_BTN)
LOG_LED: J7.9, LOG.2, U1.B2 (LOG_LED)
MEAS: D3.C, D6.C, MEAS.2, MEAS.4 (2)
MODULE_RDY: J7.7, U1.A12 (MODULE_RDY)
unnamed: R8.1, S2.3 (2), S2.4 (2)
unnamed: D4.A, R11.1
unnamed: PPS.1, R11.2
unnamed: F1.2, MEAS.1, MEAS.3 (1)
unnamed: U1.AC16 (REF_OUT), U1.AC17 (REF_IN)
unnamed: D8.A, R4.1
unnamed: GP.1, R4.2
unnamed: D7.A, R10.1
unnamed: U1.M23 (2V8_IN), U1.N23 (2V8_OUT)
unnamed: D5.A, R12.1
unnamed: LOG.1, R12.2
unnamed: PWR.1, R10.2
unnamed: R5.1, U1.AC3 (SYNC)
PMIC_ON_REQ: J7.10, U1.B16 (PMIC_ON_REQ)
PPS: E2.SIG (SIGNAL), TP1.2, U2.4 (Y)
PPS_3V3: J10.4, PPS.2, TP1.1
PPS_18V: U1.AC8 (PPS), U2.2 (A)
SD_CLK: J3.5 (CLK/SCK), U1.AA1 (SD_CLK)
SD_CMD: J3.3 (CMD/SDI), R2.1, U1.AB1 (SD_CMD)
SD_DATA: J3.7 (DAT0/SDO), R3.1, U1.Y1 (SD_DATA)
VANT: FB1.2, U1.P23 (VANT), U1.R23 (VANT)
VIN: D3.A, J2.1, J7.4, J12.1
V_BAT: J7.5, U1.B8 (VDD_BAT), VB.2
V_USB: D1.5 (VCC), D6.A, J5.VBUS1 (VBUS), J5.VBUS2 (VBUS), J7.3, JP1.VBUS (1), U1.A8 (V_USB)

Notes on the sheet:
v10
Board thickness: 1.6mm
Er: 4.6
Copper Thickness (1oz): 1.4mil/0.035mm
RF Trace Width: 13.74mil/0.349mm
Polygon Isolation: 8mil/0.2032mm
No clean process
Dielectric thickness (layer 1 to 2): 0.2mm
https://chemandy.com/calculators/coplanar-waveguide-with-ground-calculator.htm
Coplanar Waveguide Calculation:
USB and 3.3V Regulation
N. Seidle
Cut jumper to disable LED
Stat LEDs
Connections
microSD
Can GP and LOG LEDs be directly driven from module?
Does the log button have a pull up?
BLM18PG471SN1D
Pulse-Per-Second
External V_BAT
Cut trace to attach external supply to V_BAT input for Standby mode

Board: 4 copper layers, 169 parts (68 on the bottom side), 58 nets, no tracks yet.

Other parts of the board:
LOGO1: SFE_LOGO_NAME_FLAME10_MM; SFE_LOGO_NAME_FLAME_10MM
U$1: MOSAIC_0
U$3: GNSS_1
U$4: TRIBAND_2
U$5: MEAS0
U$6, U$135: _ACTIVE_ANT1
U$7: #0
U$8: C4
U$9: D#2
U$10: D#3
U$11: G0
U$12: R5
U$13: RST0
U$14: RX7
U$15: TX6
U$16: V8
U$17: #1
U$18, U$82: COM30
U$21, U$136: TIME0
U$25, U$137: PULSE1
U$31: LOG0
U$69, U$134: L1#2#50
U$78: GP1
U$79: LOG2
U$80: PPS0
U$81: PWR3
U$83, U$99: COM20
U$84, U$109: COM10
U$85, U$108: COM40
U$87, U$93, U$110, U$114: #3#3V#1
U$88, U$100: #CTS#4
U$89, U$95, U$113, U$117: #GND#0
U$90, U$101: #RTS#5
U$91, U$102, U$111: #RX#2
U$92, U$103, U$112: #TX#3
U$94, U$104: #CTS_#4
U$96, U$105: #RTS_#5
U$97, U$106, U$115: #RX_#2
U$98, U$107, U$116: #TX_#3
U$118: ##RST##2
U$119: #GP_LED#4
U$120: #LOG#5
U$121: #PMIC#6
U$122: #RDY#3
U$123, U$130: #VIN#1
U$124, U$131: #VUSB#0
U$125, U$132: #V_BAT#7
U$126: #LOG_LED_#5
U$127: #PMIC_#6
U$128: #GP_LED_#4
U$129: #RDY_#3
U$133: #_#RST##2
U$138: GNSS1
U$139: MOSAIC0
U$140: TRIBAND2
U$141: #LOG_LED#2
U$142: #PPS_LED#1
U$143: #GP_LED#3
U$144: #PWR_LED#0
U$145: #V_BAT#4
U$146: #A#8
U$147: #B#10
U$148: #EVENTA_#9
U$149: #EVENTB#11
U$150: #GP1#0
U$151: #GP1_#2
U$152: #GP2#1
U$153: #GP2_#3
U$154: #LOG#4
U$155: #LOG_BTN_#5
U$156: #PPS#6
U$157: #PPS_#7

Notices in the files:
parts and their libraries:
SparkFun-Resistors: Licensing: Creative Commons ShareAlike 4.0 International - https://creativecommons.org/licenses/by-sa/4.0
SparkFun-Aesthetics: Released under the Creative Commons Attribution Share-Alike 4.0 License
SparkFun-Aesthetics: https://creativecommons.org/licenses/by-sa/4.0
